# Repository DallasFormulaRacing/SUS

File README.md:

### Schematic

### PCB 3D Model

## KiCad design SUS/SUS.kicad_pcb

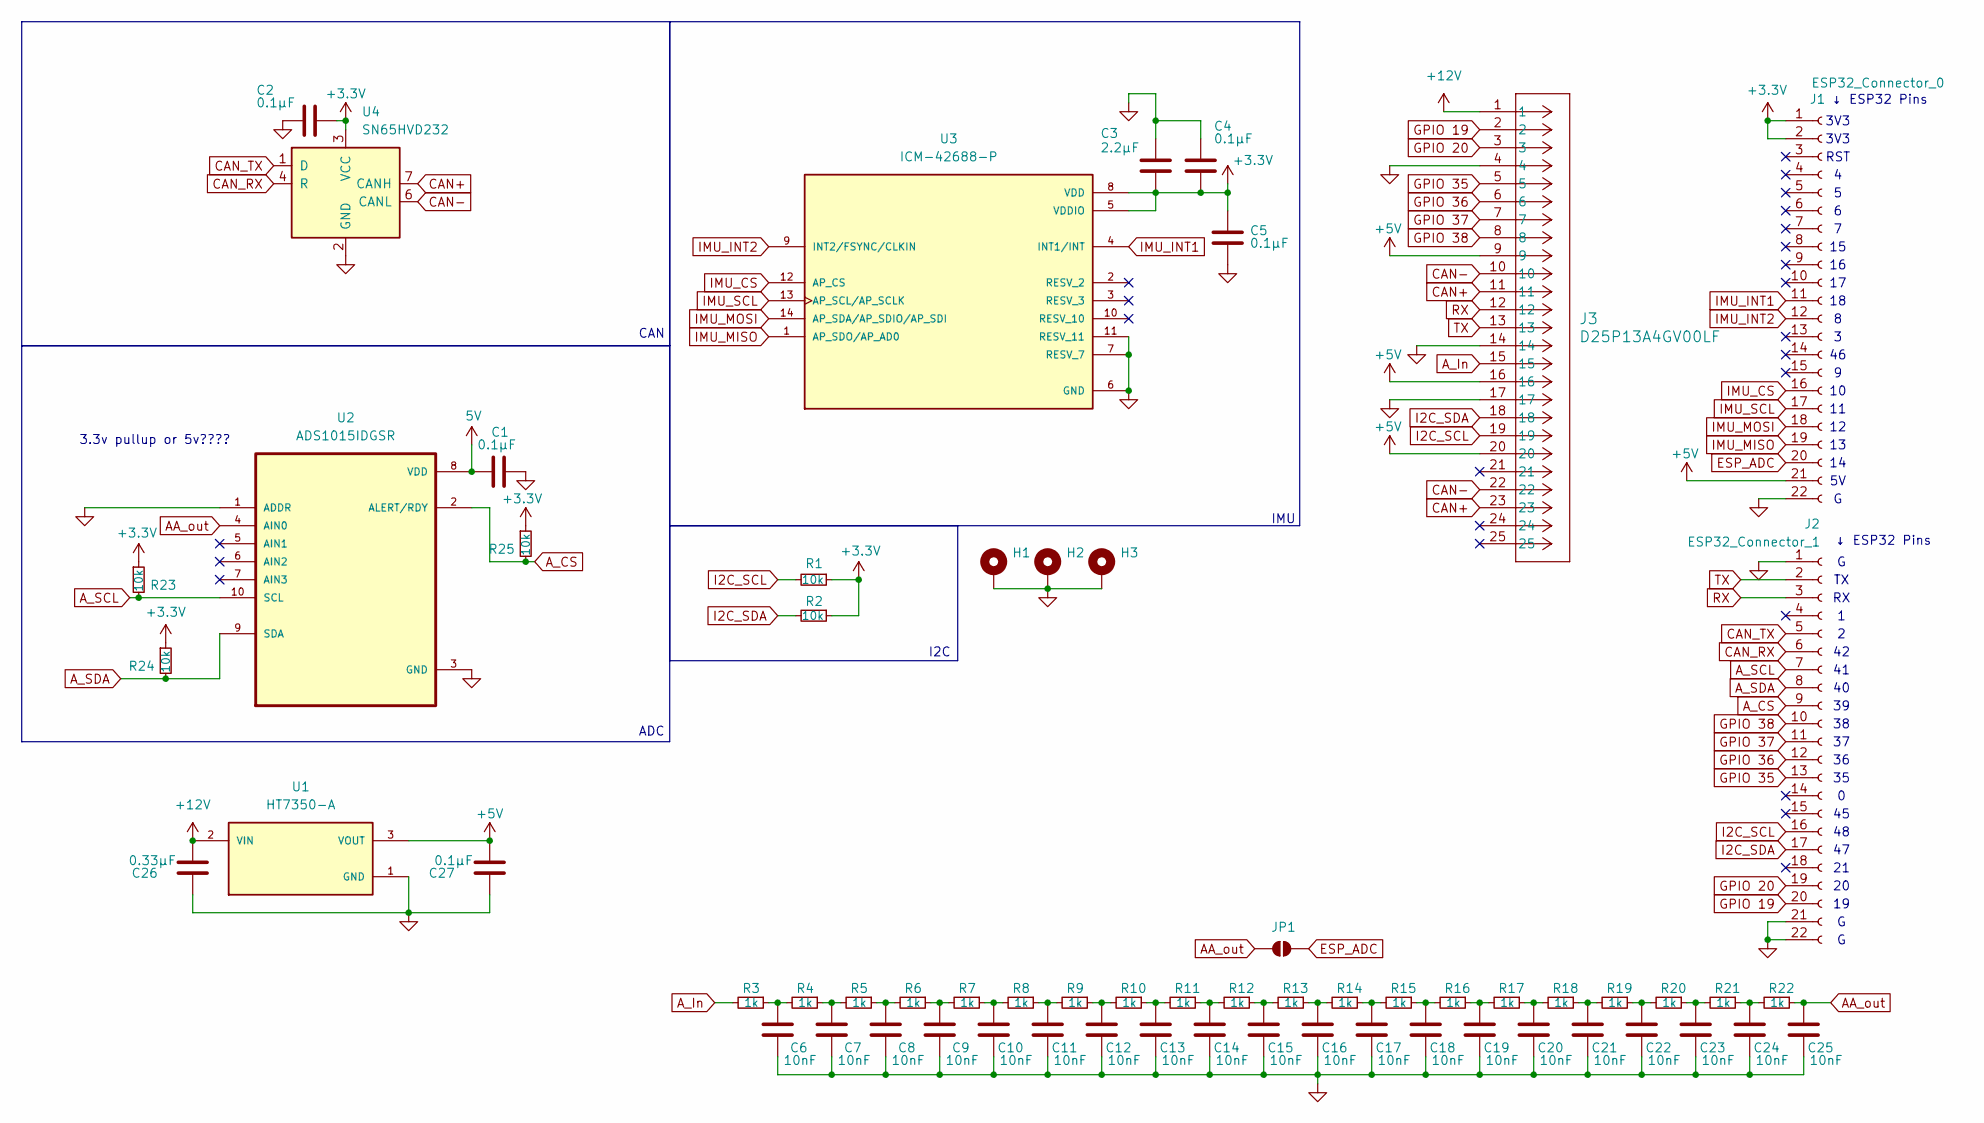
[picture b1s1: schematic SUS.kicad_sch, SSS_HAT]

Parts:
C1: 0.1μF; C_0201_0603Metric
C2, C4, C5: 0.1μF; C_0402_1005Metric_Pad0.74x0.62mm_HandSolder
C3: 2.2μF; C_0402_1005Metric_Pad0.74x0.62mm_HandSolder
C6, C7, C8, C9, C10, C11, C12, C13, C14, C15, C16, C17, C18, C19, C20, C21, C22, C23, C24, C25: 10nF; C_0201_0603Metric
C26: 0.33μF; C_0603_1608Metric
C27: 0.1μF; C_0603_1608Metric
H1, H2, H3: MountingHole_Pad; MountingHole_2.2mm_M2_Pad_TopOnly
J1: ESP32_Connector_0; PinSocket_1x22_P2.54mm_Vertical
J2: ESP32_Connector_1; PinSocket_1x22_P2.54mm_Vertical
J3: D25P13A4GV00LF; CONN_D25P_AMP
JP1: SolderJumper_2_Open; SolderJumper-2_P1.3mm_Open_TrianglePad1.0x1.5mm
R1, R2: 10k; R_0402_1005Metric_Pad0.72x0.64mm_HandSolder; JLCpart# C2906988
R3, R4, R5, R6, R7, R8, R9, R10, R11, R12, R13, R14, R15, R16, R17, R18, R19, R20, R21, R22: 1k; C_0201_0603Metric; JLCpart# C2906988
R23, R24, R25: 10k; C_0201_0603Metric; JLCpart# C2906988
U1: HT7350-A; IC_HT7333; PARTREV 1.80
U2: ADS1015IDGSR; SOP50P490X110-10N
U3: ICM-42688-P; PQFN50P300X250X97-14N; PARTREV 1.2
U4: SN65HVD232; SOIC-8_3.9x4.9mm_P1.27mm

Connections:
5V: C1.1, U2.8 (VDD)
+3.3V: C2.1, C3.2, C4.2, C5.1, J1.1, J1.2, R1.1, R2.1, R23.1, R24.1, R25.1, U3.5 (VDDIO), U3.8 (VDD), U4.3 (VCC); also elsewhere on the board
+12V: C26.2, J3.1, U1.2 (VIN)
AA_out: C25.2, JP1.1 (A), R22.1, U2.4 (AIN0)
A_CS: J2.9, R25.2, U2.2 (ALERT/RDY)
A_In: J3.15, R3.2
A_SCL: J2.7, R23.2, U2.10 (SCL)
A_SDA: J2.8, R24.2, U2.9 (SDA)
CAN+: J3.11, J3.23, U4.7 (CANH)
CAN-: J3.10, J3.22, U4.6 (CANL)
CAN_RX: J2.6, U4.4 (R)
CAN_TX: J2.5, U4.1 (D)
ESP_ADC: J1.20, JP1.2 (B)
GND: C1.2, C2.2, C3.1, C4.1, C5.2, C6.1, C7.1, C8.1, C9.1, C10.1, C11.1, C12.1, C13.1, C14.1, C15.1, C16.1, C17.1, C18.1, C19.1, C20.1, C21.1, C22.1, C23.1, C24.1, C25.1, C26.1, C27.1, H1.1, H2.1, H3.1, J1.22, J2.1, J2.21, J2.22, J3.4, J3.14, J3.17, U1.1 (GND), U2.1 (ADDR), U2.3 (GND), U3.6 (GND), U3.7 (RESV_7), U3.11 (RESV_11), U4.2 (GND)
GPIO 19: J2.20, J3.2
GPIO 20: J2.19, J3.3
GPIO 35: J2.13, J3.5
GPIO 36: J2.12, J3.6
GPIO 37: J2.11, J3.7
GPIO 38: J2.10, J3.8
I2C_SCL: J2.16, J3.19, R1.2
I2C_SDA: J2.17, J3.18, R2.2
IMU_CS: J1.16, U3.12 (AP_CS)
IMU_INT1: J1.11, U3.4 (INT1/INT)
IMU_INT2: J1.12, U3.9 (INT2/FSYNC/CLKIN)
IMU_MISO: J1.19, U3.1 (AP_SDO/AP_AD0)
IMU_MOSI: J1.18, U3.14 (AP_SDA/AP_SDIO/AP_SDI)
IMU_SCL: J1.17, U3.13 (AP_SCL/AP_SCLK)
unnamed: C6.2, R3.1, R4.2
unnamed: C7.2, R4.1, R5.2
unnamed: C8.2, R5.1, R6.2
unnamed: C9.2, R6.1, R7.2
unnamed: C10.2, R7.1, R8.2
unnamed: C11.2, R8.1, R9.2
unnamed: C12.2, R9.1, R10.2
unnamed: C13.2, R10.1, R11.2
unnamed: C14.2, R11.1, R12.2
unnamed: C15.2, R12.1, R13.2
unnamed: C16.2, R13.1, R14.2
unnamed: C17.2, R14.1, R15.2
unnamed: C18.2, R15.1, R16.2
unnamed: C19.2, R16.1, R17.2
unnamed: C20.2, R17.1, R18.2
unnamed: C21.2, R18.1, R19.2
unnamed: C22.2, R19.1, R20.2
unnamed: C23.2, R20.1, R21.2
unnamed: C24.2, R21.1, R22.2
RX: J2.3, J3.12
TX: J2.2, J3.13

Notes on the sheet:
↓ ESP32 Pins
3V3
3.3v pullup or 5v????
ADC
I2C
CAN
IMU
RST

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
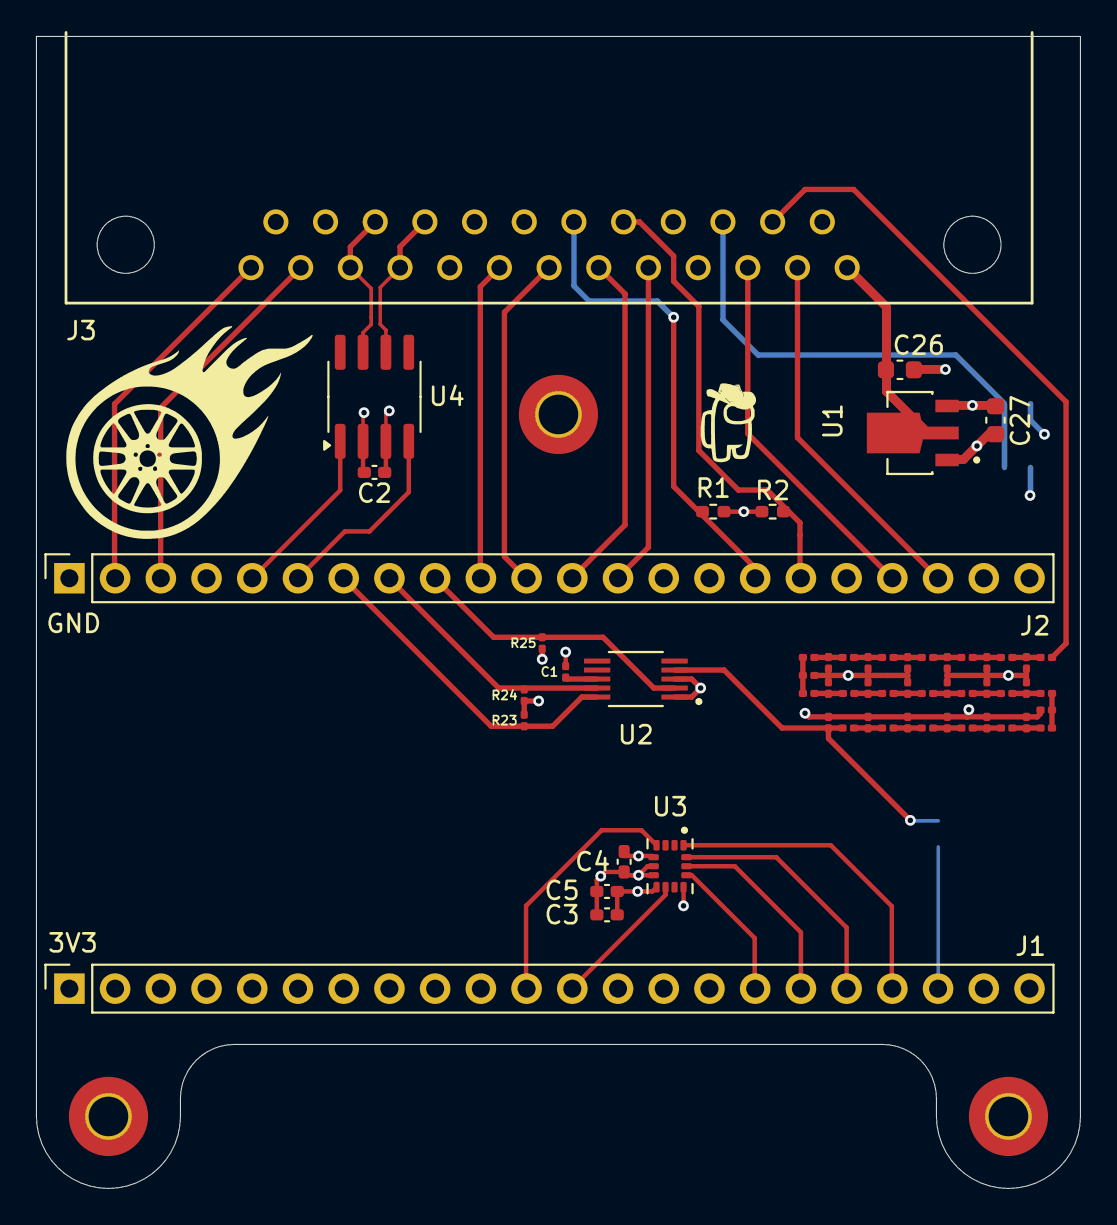
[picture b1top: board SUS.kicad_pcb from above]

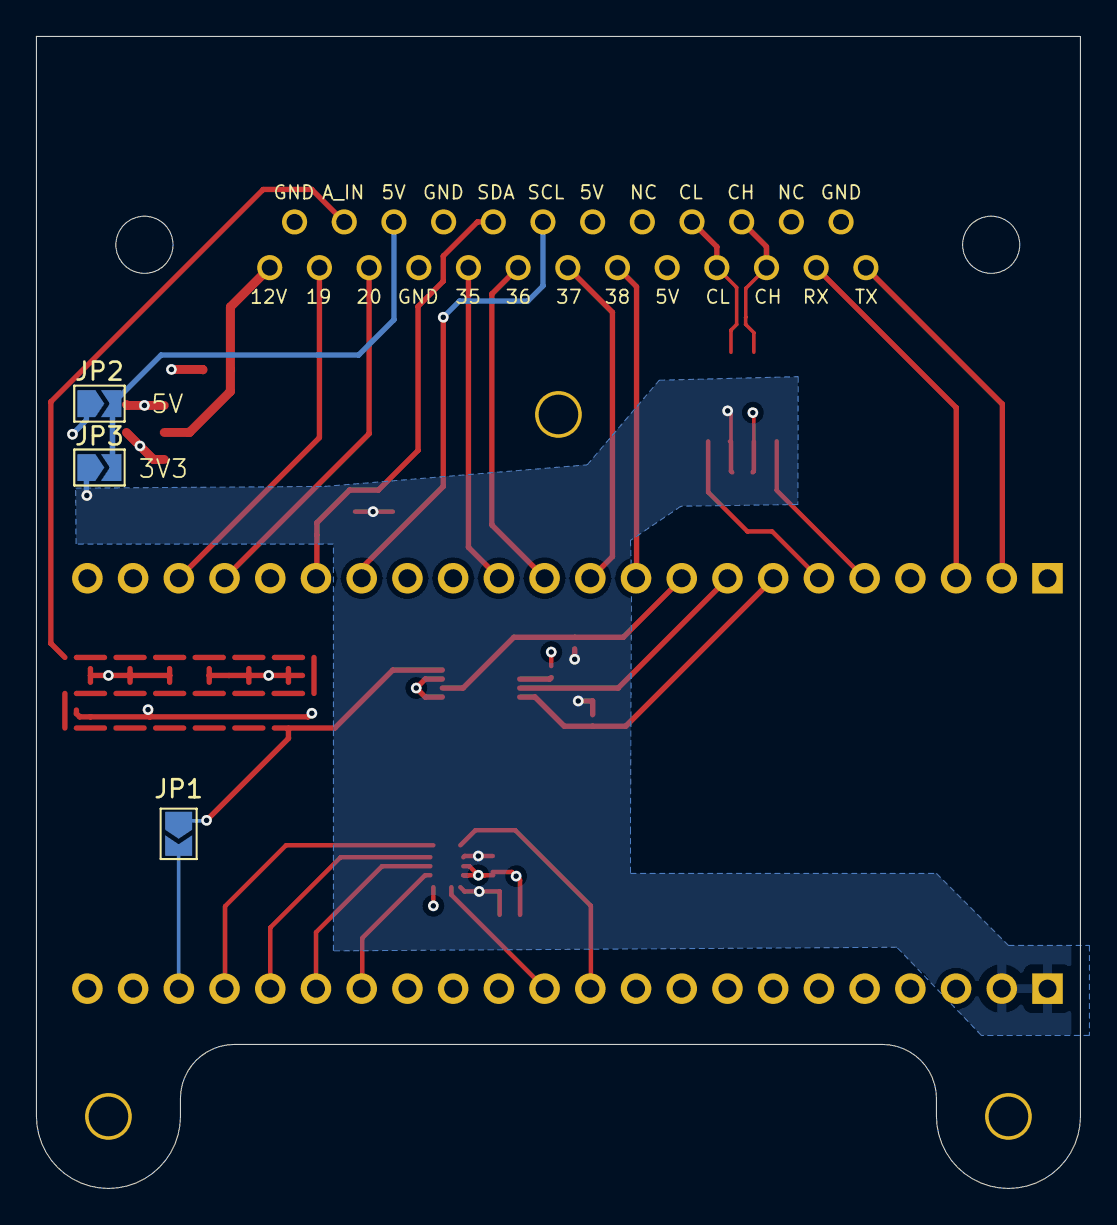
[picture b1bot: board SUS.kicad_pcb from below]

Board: 4 copper layers, 58.0 x 64.0 mm, 65 parts (3 on the bottom side), 51 nets.

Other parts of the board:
JP2, JP3: SolderJumper_2_Open; SolderJumper-2_P1.3mm_Open_TrianglePad1.0x1.5mm

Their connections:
+3.3V: JP3.1 (A); also elsewhere on the board

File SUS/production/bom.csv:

Designator,Footprint,Quantity,Value,LCSC Part #
C1,0201,1,0.1μF,
"C10, C11, C12, C13, C14, C15, C16, C17, C18, C19, C20, C21, C22, C23, C24, C25, C6, C7, C8, C9",0201,20,10nF,
"C2, C4, C5",0402,3,0.1μF,
C26,0603,1,0.33μF,
C27,0603,1,0.1μF,
C3,0402,1,2.2μF,
J1,PinSocket_1x22_P2.54mm_Vertical,1,ESP32_Connector_0,
J2,PinSocket_1x22_P2.54mm_Vertical,1,ESP32_Connector_1,
J3,CONN_D25P_AMP,1,D25P13A4GV00LF,
"R1, R2",0402,2,10k,
"R10, R11, R12, R13, R14, R15, R16, R17, R18, R19, R20, R21, R22, R3, R4, R5, R6, R7, R8, R9",0201,20,1k,
"R23, R24, R25",0201,3,10k,
U1,IC_HT7333,1,HT7350-A,
U2,SOP50P490X110-10N,1,ADS1015IDGSR,
U3,PQFN50P300X250X97-14N,1,ICM-42688-P,
U4,SOIC-8_3.9x4.9mm_P1.27mm,1,SN65HVD232,

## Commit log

2024-10-22 PCB Schematic Upload
2024-10-22 Changed file organization
2024-10-22 Added 2 CAN buses and 2 I2C buses
2024-10-23 Removed 1 I2C bus & 1 CAN transciever
2024-10-23 Added 2 Channel 18-bit ADC
2024-10-23 added IMU
2024-10-24 Routed PCB & Replaced IMU for ICM-42688-P
2024-10-24 Changed a few traces and added measurements to PCB drawing
2024-10-24 A few minor layout changes
2024-10-24 Changed PCB drawing size & updated README.md images
2024-10-24 Fixed PCB drawing
2024-10-24 Added DFR logo and fixed GND connections
2024-10-29 Added ADS8320EB/250 ADC
2024-10-31 Replaced ADC for ADS8320EB-250, changed molex connectors to hirose connectors and re-routed PCB
2024-10-31 Updated 3D model & readme.
2024-10-31 Edited Readme.md and added to silkscreen
2024-11-05 Fixed J1 & J2 footprints which called for an entire re-route
2024-11-06 added updates from 11/5 meeting. Faraday cage WIP
2024-11-06 Rename SSS_HAT to SUS
2024-11-06 Changed the layout of a few compoenents, added EMI cage & updated README.md
2024-11-06 Changed ESP32 analog pin
2024-11-07 Re-reouted wheel speed signal line
2024-11-07 Fixed width of wheel speed data line
2024-11-07 Minor fixes & generated fabrication files
2024-11-07 Updated trace names & README.md
2024-11-07 Minor fixes
2024-11-08 added pads to connect 3.3v or 5v to lin pots & other last minute changes
2024-11-15 Removed Vias
2024-11-15 updated production files
2025-03-25 Complete re-design. Readme still needs to be updated.
2025-03-27 Changed CAN transceiver.
2025-03-30 Fixed DRC errors
2025-03-30 Minor Changes
2025-04-02 Added jumpers for 5v and 3v3 for lin pot
2025-04-19 Updated Schematic.pdf & README
